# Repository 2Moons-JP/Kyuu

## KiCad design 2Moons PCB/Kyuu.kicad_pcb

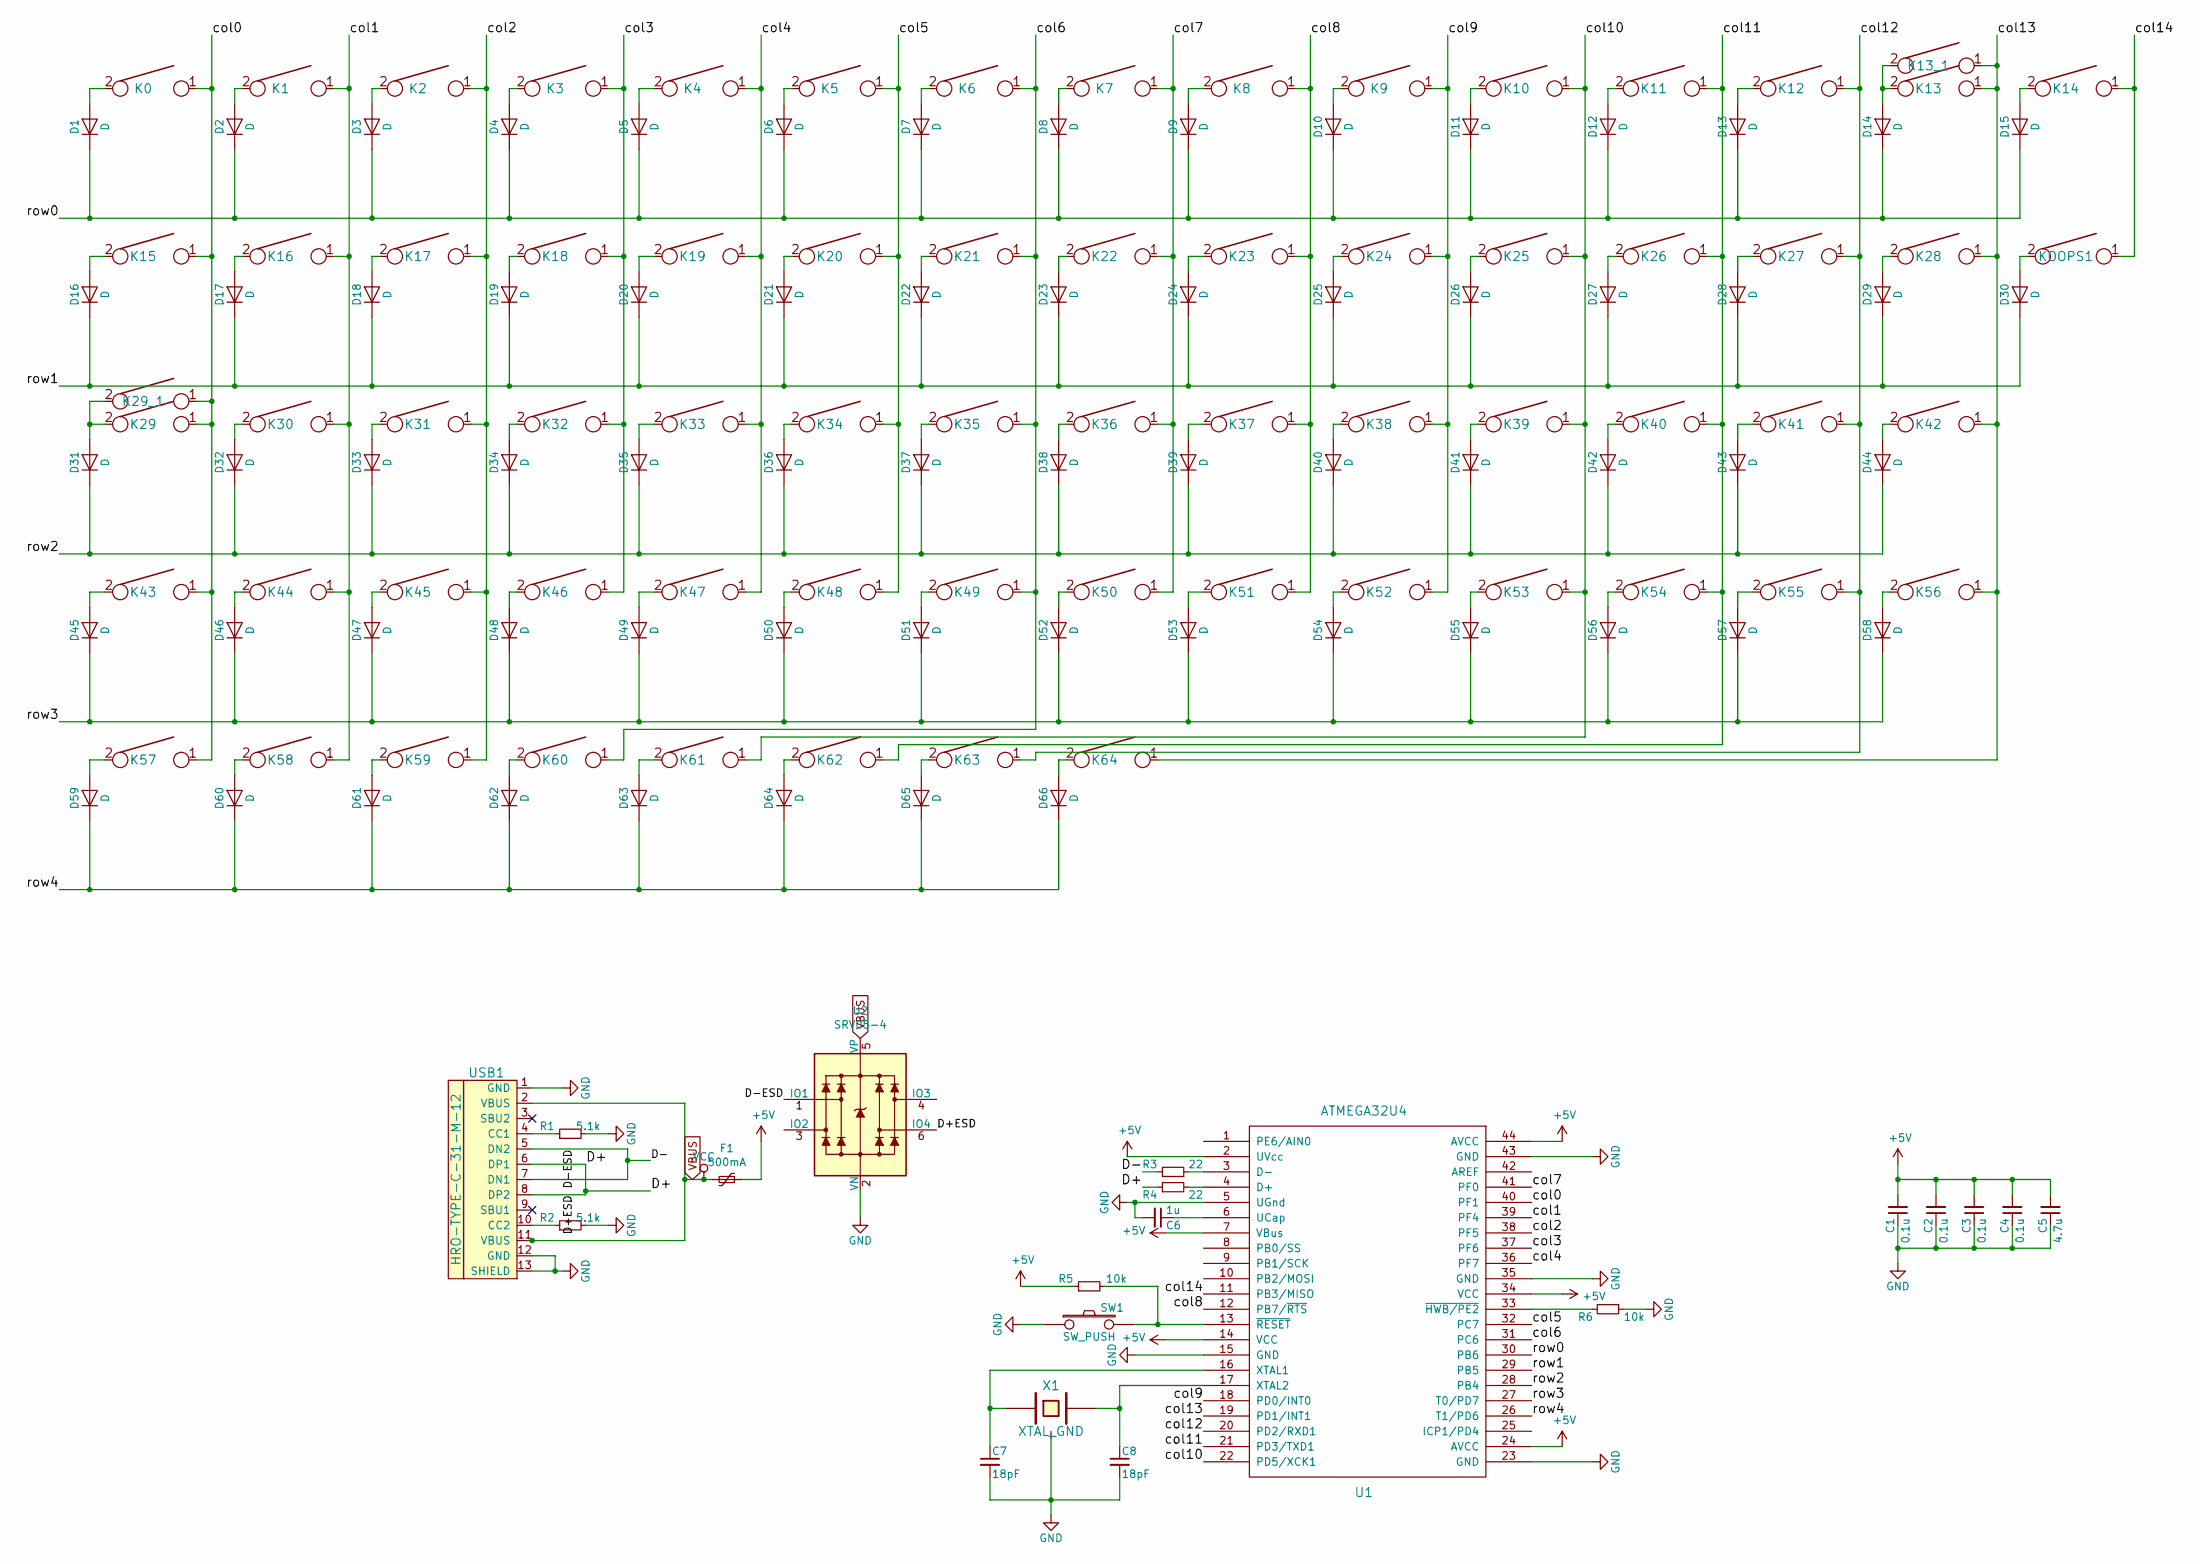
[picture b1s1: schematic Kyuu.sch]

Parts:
C1, C2, C3, C4: 0.1u; C_0603_HandSoldering; Part# CC0603KRX7R9BB104; LCSC Part# C14663
C5: 4.7u; C_0603_HandSoldering; Part# CL10A475KO8NNNC; LCSC Part# C19666
C6: 1u; C_0603_HandSoldering; Part# CC0603KRX7R9BB104; LCSC Part# C14663
C7, C8: 18pF; C_0603_HandSoldering; Part# CL10C180JB8NNNC; LCSC Part# C1647
D1, D2, D3, D4, D5, D6, D7, D8, D9, D10, D11, D12, D13, D14, D15, D16, D17, D18, D19, D20, D21, D22, D23, D24, D25, D26, D27, D28, D29, D30, D31, D32, D33, D34, D35, D36, D37, D38, D39, D40, D41, D42, D43, D44, D45, D46, D47, D48, D49, D50, D51, D52, D53, D54, D55, D56, D57, D58, D59, D60, D61, D62, D63, D64, D65, D66: D; D_SOD-123; Part# 1N4148W; LCSC Part# C81598
F1: 500mA; Fuse_1206_3216Metric; Part# nSMD025; LCSC Part# C70068
K0, K1, K2, K3, K4, K5, K6, K7, K8, K9, K10, K11, K12, K13_1, K14, K16, K17, K18, K19, K20, K21, K22, K23, K24, K25, K26, K27, K30, K31, K32, K33, K34, K35, K36, K37, K38, K39, K40, K42, K44, K45, K46, K47, K48, K49, K50, K51, K52, K53, K55, K56, K58, K62, K63, K64: KEYSW; CHERRY_PCB_100H
K13: KEYSW; CHERRY_PCB_200H
K15, K28, K57, K59, K61: KEYSW; CHERRY_PCB_150H
K29, K54: KEYSW; CHERRY_PCB_175H
K29_1: KEYSW; CHERRY_PCB_125H
K41, K43: KEYSW; CHERRY_PCB_225H
K60: KEYSW; CHERRY_PCB_7H
KOOPS1: KEYSW; CHERRY_PCB_100H
R1, R2: 5.1k; R_0603_HandSoldering; Part# 0603WAF5101T5E; LCSC Part# C23186
R3, R4: 22; R_0603_HandSoldering; Part# 0603WAF220JT5E; LCSC Part# C23345
R5, R6: 10k; R_0603_HandSoldering; Part# 0603WAF1002T5E; LCSC Part# C25804
SW1: SW_PUSH; SW_SPST_TL3342; Part# RS-187R05A2-DSMTRT; LCSC Part# C221929
U1: ATMEGA32U4; TQFP-44_10x10mm_Pitch0.8mm; Part# ATMEGA32U4-AU; LCSC Part# C44854
U2: SRV05-4; SOT-23-6_Handsoldering; Part# SRV05-4; LCSC Part# C127538
USB1: HRO-TYPE-C-31-M-12; HRO-TYPE-C-31-M-12-HandSoldering; Part# TYPE-C-31-M-12; LCSC Part# C165948
X1: XTAL_GND; FA-238; Part# TAXM16M4RDBCCT2T; LCSC Part# C164044

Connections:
+5V: C1.2, C2.2, C3.2, C4.2, C5.2, F1.1, R5.1, U1.2 (UVcc), U1.7 (VBus), U1.14 (VCC), U1.24 (AVCC), U1.34 (VCC), U1.44 (AVCC)
/D+: R4.1, U2.6 (IO4), USB1.6 (DP1), USB1.8 (DP2)
/D-: R3.1, U2.1 (IO1), USB1.5 (DN2), USB1.7 (DN1)
/col0: K0.1, K15.1, K29.1, K29_1.1, K43.1, K57.1, U1.40 (PF1)
/col1: K1.1, K16.1, K30.1, K44.1, K58.1, U1.39 (PF4)
/col2: K2.1, K17.1, K31.1, K45.1, K59.1, U1.38 (PF5)
/col3: K3.1, K18.1, K32.1, K46.1, U1.37 (PF6)
/col4: K4.1, K19.1, K33.1, K47.1, U1.36 (PF7)
/col5: K5.1, K20.1, K34.1, K48.1, U1.32 (PC7)
/col6: K6.1, K21.1, K35.1, K49.1, K60.1, U1.31 (PC6)
/col7: K7.1, K22.1, K36.1, K50.1, U1.41 (PF0)
/col8: K8.1, K23.1, K37.1, K51.1, U1.12 (PB7/~RTS)
/col9: K9.1, K24.1, K38.1, K52.1, U1.18 (PD0/INT0)
/col10: K10.1, K25.1, K39.1, K53.1, K61.1, U1.22 (PD5/XCK1)
/col11: K11.1, K26.1, K40.1, K54.1, K62.1, U1.21 (PD3/TXD1)
/col12: K12.1, K27.1, K41.1, K55.1, K63.1, U1.20 (PD2/RXD1)
/col13: K13.1, K13_1.1, K28.1, K42.1, K56.1, K64.1, U1.19 (PD1/INT1); also elsewhere on the board
/col14: K14.1, KOOPS1.1, U1.11 (PB3/MISO)
/row0: D1.1 (K), D2.1 (K), D3.1 (K), D4.1 (K), D5.1 (K), D6.1 (K), D7.1 (K), D8.1 (K), D9.1 (K), D10.1 (K), D11.1 (K), D12.1 (K), D13.1 (K), D14.1 (K), D15.1 (K), U1.30 (PB6)
/row1: D16.1 (K), D17.1 (K), D18.1 (K), D19.1 (K), D20.1 (K), D21.1 (K), D22.1 (K), D23.1 (K), D24.1 (K), D25.1 (K), D26.1 (K), D27.1 (K), D28.1 (K), D29.1 (K), D30.1 (K), U1.29 (PB5)
/row2: D31.1 (K), D32.1 (K), D33.1 (K), D34.1 (K), D35.1 (K), D36.1 (K), D37.1 (K), D38.1 (K), D39.1 (K), D40.1 (K), D41.1 (K), D42.1 (K), D43.1 (K), D44.1 (K), U1.28 (PB4); also elsewhere on the board
/row3: D45.1 (K), D46.1 (K), D47.1 (K), D48.1 (K), D49.1 (K), D50.1 (K), D51.1 (K), D52.1 (K), D53.1 (K), D54.1 (K), D55.1 (K), D56.1 (K), D57.1 (K), D58.1 (K), U1.27 (T0/PD7)
/row4: D59.1 (K), D60.1 (K), D61.1 (K), D62.1 (K), D63.1 (K), D64.1 (K), D65.1 (K), D66.1 (K), U1.26 (T1/PD6)
GND: C1.1, C2.1, C3.1, C4.1, C5.1, C6.2, C7.2, C8.2, R1.2, R2.2, R6.1, SW1.1, U1.5 (UGnd), U1.15 (GND), U1.23 (GND), U1.35 (GND), U1.43 (GND), U2.2 (VN), USB1.1 (GND), USB1.12 (GND), USB1.13 (SHIELD), X1.3
unnamed: C6.1, U1.6 (UCap)
unnamed: C7.1, U1.16 (XTAL1), X1.1
unnamed: C8.1, U1.17 (XTAL2), X1.2
unnamed: D1.2 (A), K0.2
unnamed: D2.2 (A), K1.2
unnamed: D3.2 (A), K2.2
unnamed: D4.2 (A), K3.2
unnamed: D5.2 (A), K4.2
unnamed: D6.2 (A), K5.2
unnamed: D7.2 (A), K6.2
unnamed: D8.2 (A), K7.2
unnamed: D9.2 (A), K8.2
unnamed: D10.2 (A), K9.2
unnamed: D11.2 (A), K10.2
unnamed: D12.2 (A), K11.2
unnamed: D13.2 (A), K12.2
unnamed: D14.2 (A), K13.2, K13_1.2
unnamed: D15.2 (A), K14.2
unnamed: D16.2 (A), K15.2
unnamed: D17.2 (A), K16.2
unnamed: D18.2 (A), K17.2
unnamed: D19.2 (A), K18.2
unnamed: D20.2 (A), K19.2
unnamed: D21.2 (A), K20.2
unnamed: D22.2 (A), K21.2
unnamed: D23.2 (A), K22.2
unnamed: D24.2 (A), K23.2
unnamed: D25.2 (A), K24.2
unnamed: D26.2 (A), K25.2
unnamed: D27.2 (A), K26.2
unnamed: D28.2 (A), K27.2
unnamed: D29.2 (A), K28.2
unnamed: D30.2 (A), KOOPS1.2
unnamed: D31.2 (A), K29.2, K29_1.2
unnamed: D32.2 (A), K30.2
unnamed: D33.2 (A), K31.2
unnamed: D34.2 (A), K32.2
unnamed: D35.2 (A), K33.2
unnamed: D36.2 (A), K34.2
unnamed: D37.2 (A), K35.2
unnamed: D38.2 (A), K36.2
unnamed: D39.2 (A), K37.2
unnamed: D40.2 (A), K38.2
unnamed: D41.2 (A), K39.2
unnamed: D42.2 (A), K40.2
unnamed: D43.2 (A), K41.2
unnamed 70: D44.2 (A), K42.2; also elsewhere on the board
unnamed: D45.2 (A), K43.2
unnamed: D46.2 (A), K44.2
unnamed: D47.2 (A), K45.2
unnamed: D48.2 (A), K46.2
unnamed: D49.2 (A), K47.2
unnamed: D50.2 (A), K48.2
unnamed: D51.2 (A), K49.2
unnamed: D52.2 (A), K50.2
unnamed: D53.2 (A), K51.2
unnamed: D54.2 (A), K52.2
unnamed: D55.2 (A), K53.2
unnamed: D56.2 (A), K54.2
unnamed: D57.2 (A), K55.2
unnamed: D58.2 (A), K56.2
unnamed: D59.2 (A), K57.2
unnamed: D60.2 (A), K58.2
unnamed: D61.2 (A), K59.2
unnamed: D62.2 (A), K60.2
unnamed: D63.2 (A), K61.2
unnamed: D64.2 (A), K62.2
unnamed: D65.2 (A), K63.2
unnamed: D66.2 (A), K64.2
unnamed: R1.1, USB1.4 (CC1)
unnamed: R2.1, USB1.10 (CC2)
unnamed: R3.2, U1.3 (D-)
unnamed: R4.2, U1.4 (D+)
unnamed: R5.2, SW1.2, U1.13 (~RESET)
unnamed: R6.2, U1.33 (~HWB/PE2)
VBUS: F1.2, U2.5 (VP), USB1.2 (VBUS), USB1.11 (VBUS)

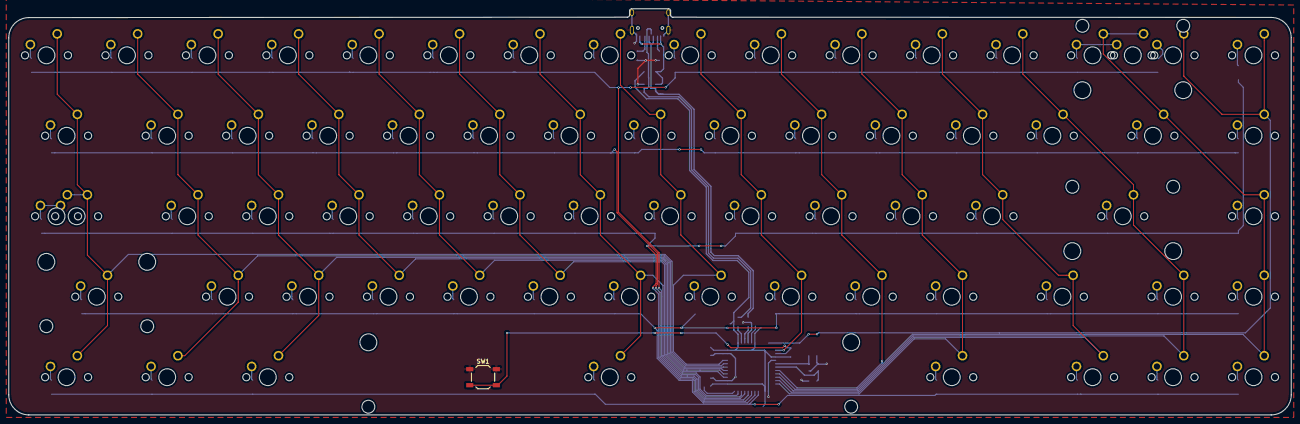
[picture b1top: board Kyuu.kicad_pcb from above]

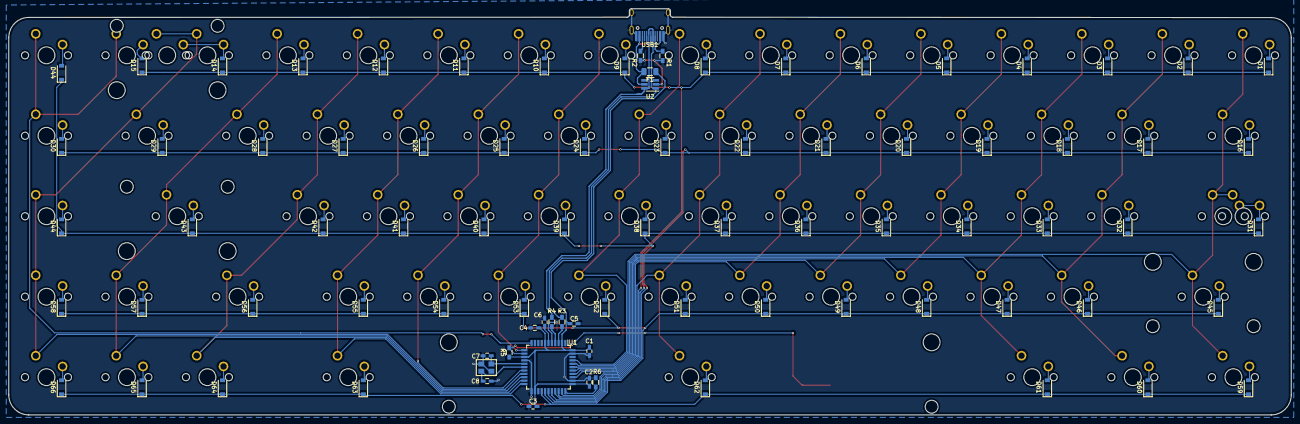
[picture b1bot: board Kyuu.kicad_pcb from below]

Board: 2 copper layers, 303.6 x 96.1 mm, 156 parts (86 on the bottom side), 100 nets.

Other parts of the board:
D44#2: D; D_SOD-123
K42#2: KEYSW; CHERRY_PCB_100H

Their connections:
/col13: K42#2.1; also elsewhere on the board
/row2: D44#2.1; also elsewhere on the board
unnamed 70: D44#2.2, K42#2.2; also elsewhere on the board

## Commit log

2021-01-23 PCB with ESD Added
2021-01-24 cache
2021-01-24 Kyuu New PCB
2021-02-07 2/8/2021
2021-02-09 Manu Prep
2021-04-12 Fixed Step
